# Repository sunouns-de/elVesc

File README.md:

# README

`Status: Completed (Archive State).`

This project is no longer being maintained as an active WIP. The primary reason is the availability of official VESC peripherals (such as the [VESC Dash 35B](https://www.vesclabs.com/product/vesc-dash-35b/) or the [VESC Rmcore](https://www.vesclabs.com/product/vesc-rmcore/)), which cover many of the original goals (CAN connectivity, LispBM scripting) natively and, in some aspects, more effectively.

**Important notes on the current state:**
1. **PCB Design:** The latest PCB design in this repository still contains errors. The board layout needs to be cross-checked against the schematics and revised before it can be considered fully functional.
2. **12V High-Side Switching:** Unlike many other solutions, including official ones like the RmCore, this design explicitly supports 12V high-side switching for vehicle lighting.
3. **Hardware Fixes:** The horn circuitry has already been corrected in the schematic but has not yet been implemented in the physical PCB layout.

## Overview

You find the code, flashable on an ESP32 DevKitC with PlatformIO in the submodule.

Everything needed for the PCB inside pcb-schematics.

Link to Onshape Design of Headunit Mount in directory 3d design.
Other project designs will also be added here.

## Core concept

Replacement for original board electronics and an open platform to have a tachometer for any [VESC](https://vesc-project.com/) powered E-Bike.

### Headunit (Display)

#### Implemented and working
Currently working on Tachometer:
- Speed
- Trip Kilometer (resets every power cycle)
- Time since Startup
- Average Speed
- Battery Voltage (mapped to left bar)
- Motor Current (mapped to right bar)
- Motor Power in kW (below right bar)
- Brake Lights
 - triggered when pulling any brake lever
 - also triggered when using regenerative braking above a configurable motor current

Currently all values (wheel diameter, battery voltage, max current, etc.) are hard coded.

Proper way for multiple bikes will be to utilize config files.

#### Implemented but not working
- Average Wh per km consumption
- Horn (probably hardware issue due to bad soldering)

#### Planned
- Odometer (saving distance to ESP32 flash)
- Don't try to calculate values like average speed or  but just get them from VESC

##### Ideas
- Smaller headunit but with more features: Utilizing also an ESP 32 C6 with Zigbee
 - Home Assistant integration
- OTA Updates
- Blinkers but requires more Pins on ESP32 or multiplexing
  - Also requires more than current 8 wires by using a normal RJ45-connector and Ethernet-cable to bottom or serial communication and therefore another microcontroller on the SPDB.

### Switching and Power Distribution Board (SPDB)

Converts high battery voltage to 12V for the headlights and other components. (DC
/DC converter is not cheap, but great quality and has pleanty of headroom)

Also provides 5V for the Headunit: ESP32, Hall-Effect-Brake-Levers and Display. (ESP32 runs on 3V but the dev kit converts the incoming 5V to the usable 3V)

Connects the VESC to the rest of the system.

Turns on Brakelights and also provides power for the 12V lights.

#### Planned
- components with bigger footprints for easier soldering
 - MOSFETs
 - capacitors
 - resistors

#### Ideas

- USB-C in port and DC/DC converter for charging big E-Bike battery (not _really_ practical but I really want this hehe)
- USB-C out port for charging other devices or at least another 12V out to use existing products for this
- Eventually blinkers (my L1E-class-bike came without them from the manufacturer so they are not mandatory)

In combination with Headunit: Serial connection / CAN-BUS based system.

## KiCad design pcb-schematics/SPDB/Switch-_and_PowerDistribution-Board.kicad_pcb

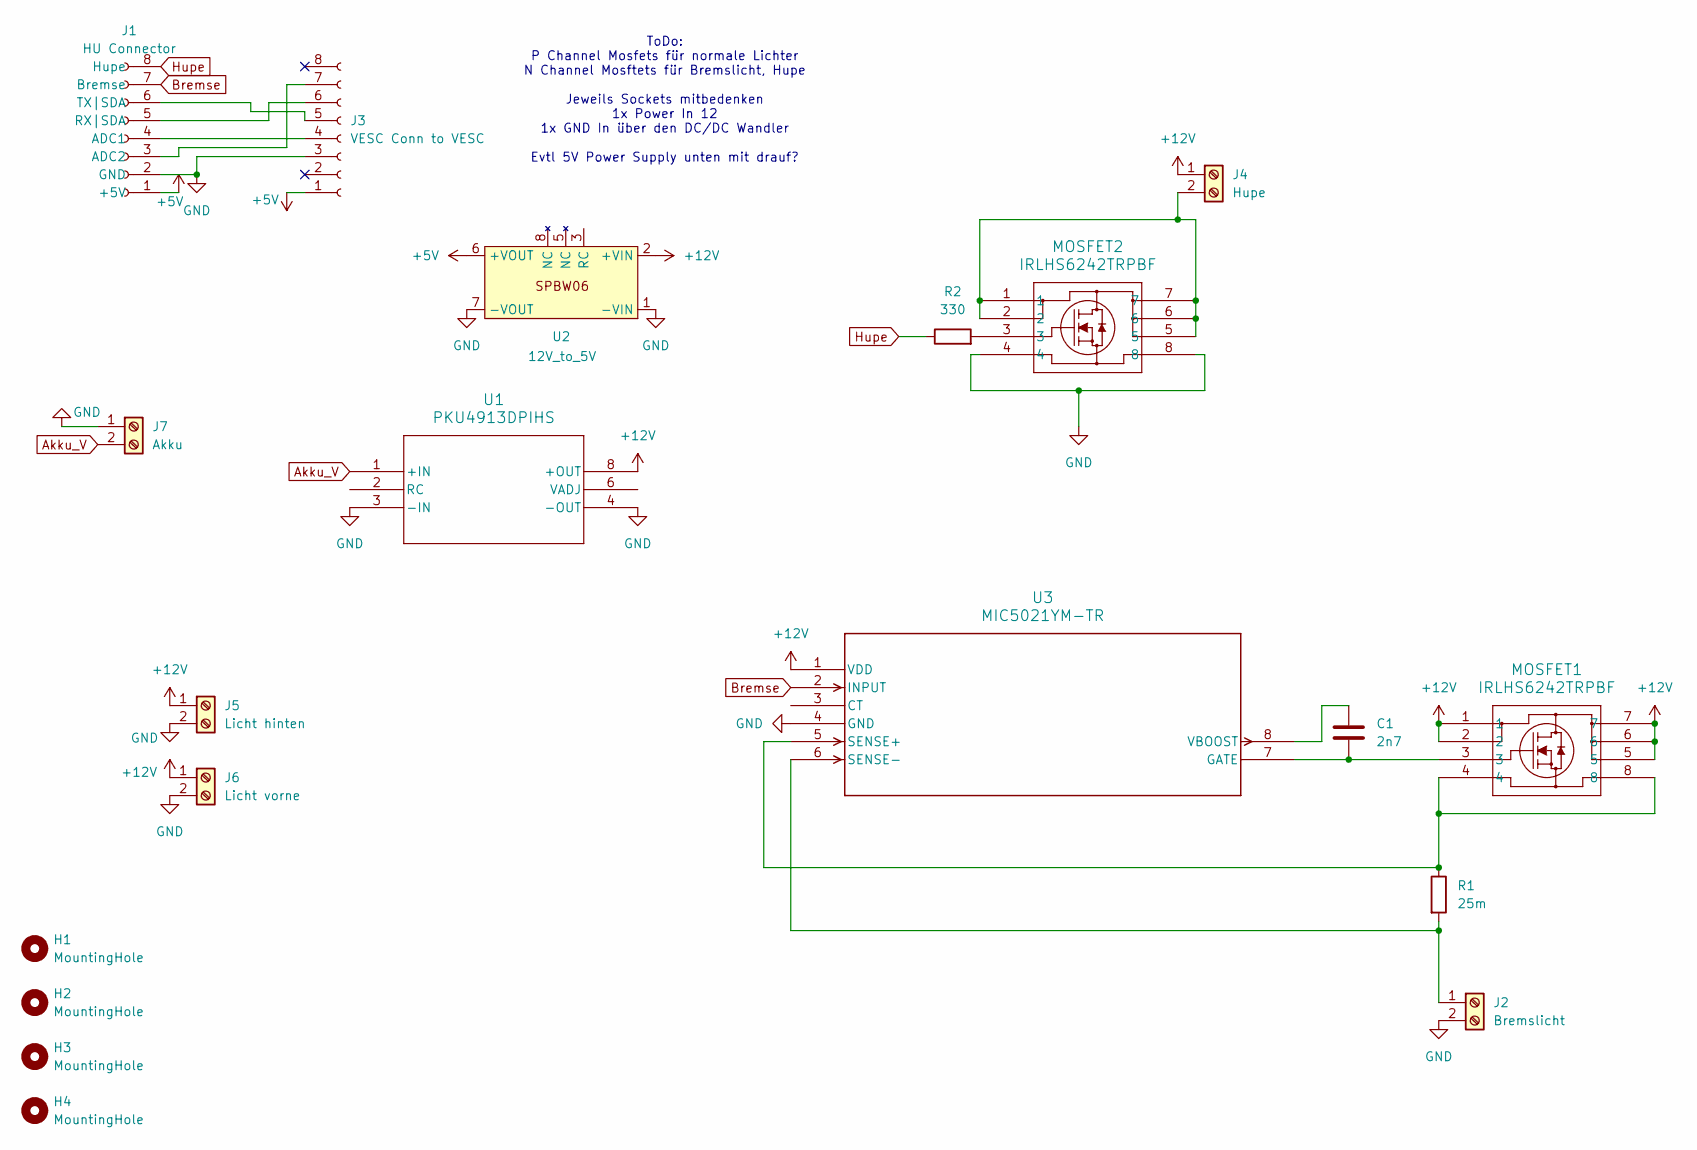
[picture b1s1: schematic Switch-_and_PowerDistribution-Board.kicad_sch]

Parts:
C1: 2n7; C_0805_2012Metric_Pad1.18x1.45mm_HandSolder
H1, H2, H3, H4: MountingHole; MountingHole_3.2mm_M3
J1: HU Connector; RJ45_Amphenol_54602-x08_Horizontal
J2: Bremslicht; TerminalBlock_bornier-2_P5.08mm
J3: VESC Conn to VESC; PinHeader_1x08_P2.54mm_Vertical
J4: Hupe; TerminalBlock_bornier-2_P5.08mm
J5: Licht hinten; TerminalBlock_bornier-2_P5.08mm
J6: Licht vorne; TerminalBlock_bornier-2_P5.08mm
J7: Akku; AMASS_XT60-F_1x02_P7.20mm_Vertical
MOSFET1, MOSFET2: IRLHS6242TRPBF; PQFN6_2X2_INF
R1: 25m; R_Axial_DIN0204_L3.6mm_D1.6mm_P5.08mm_Horizontal
R2: 330; R_Axial_DIN0204_L3.6mm_D1.6mm_P5.08mm_Horizontal
U1: PKU4913DPIHS; PKU4913DPIHS_FPM
U2: 12V_to_5V; DPBW06_MWU
U3: MIC5021YM-TR; SOIC-8_M_MCH

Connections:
+5V: J1.1 (+5V), J3.1, U2.6 (+VOUT)
+12V: J4.1, J5.1, J6.1, MOSFET1.1, MOSFET1.2, MOSFET1.5, MOSFET1.6, MOSFET1.7, U1.8 (+OUT), U2.2 (+VIN), U3.1 (VDD)
Akku_V: J7.2, U1.1 (+IN)
Bremse: J1.7 (Bremse), U3.2 (INPUT)
GND: J1.2 (GND), J2.2, J3.3, J5.2, J6.2, J7.1, MOSFET2.4, MOSFET2.8, U1.3 (-IN), U1.4 (-OUT), U2.1 (-VIN), U2.7 (-VOUT), U3.4 (GND)
Hupe: J1.8 (Hupe), R2.1
unnamed: J1.4 (ADC1), J3.4
unnamed: J1.3 (ADC2), J3.7 (Pin_2)
unnamed: J1.5 (RX|SDA), J3.6 (Pin_3)
unnamed: J1.6 (TX|SDA), J3.5 (Pin_4)
unnamed: J2.1, R1.2, U3.6 (SENSE-)
unnamed: J4.2, MOSFET2.1, MOSFET2.2, MOSFET2.5, MOSFET2.6, MOSFET2.7
unnamed: MOSFET2.3, R2.2
unnamed: C1.2, MOSFET1.3, U3.7 (GATE)
unnamed: MOSFET1.4, MOSFET1.8, R1.1, U3.5 (SENSE+)
unnamed: C1.1, U3.8 (VBOOST)

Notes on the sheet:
ToDo: P Channel Mosfets für normale Lichter N Channel Mosftets für Bremslicht, Hupe Jeweils Sockets mitbedenken 1x Power In 12 1x GND In über den DC/DC Wandler Evtl 5V Power Supply unten mit drauf?

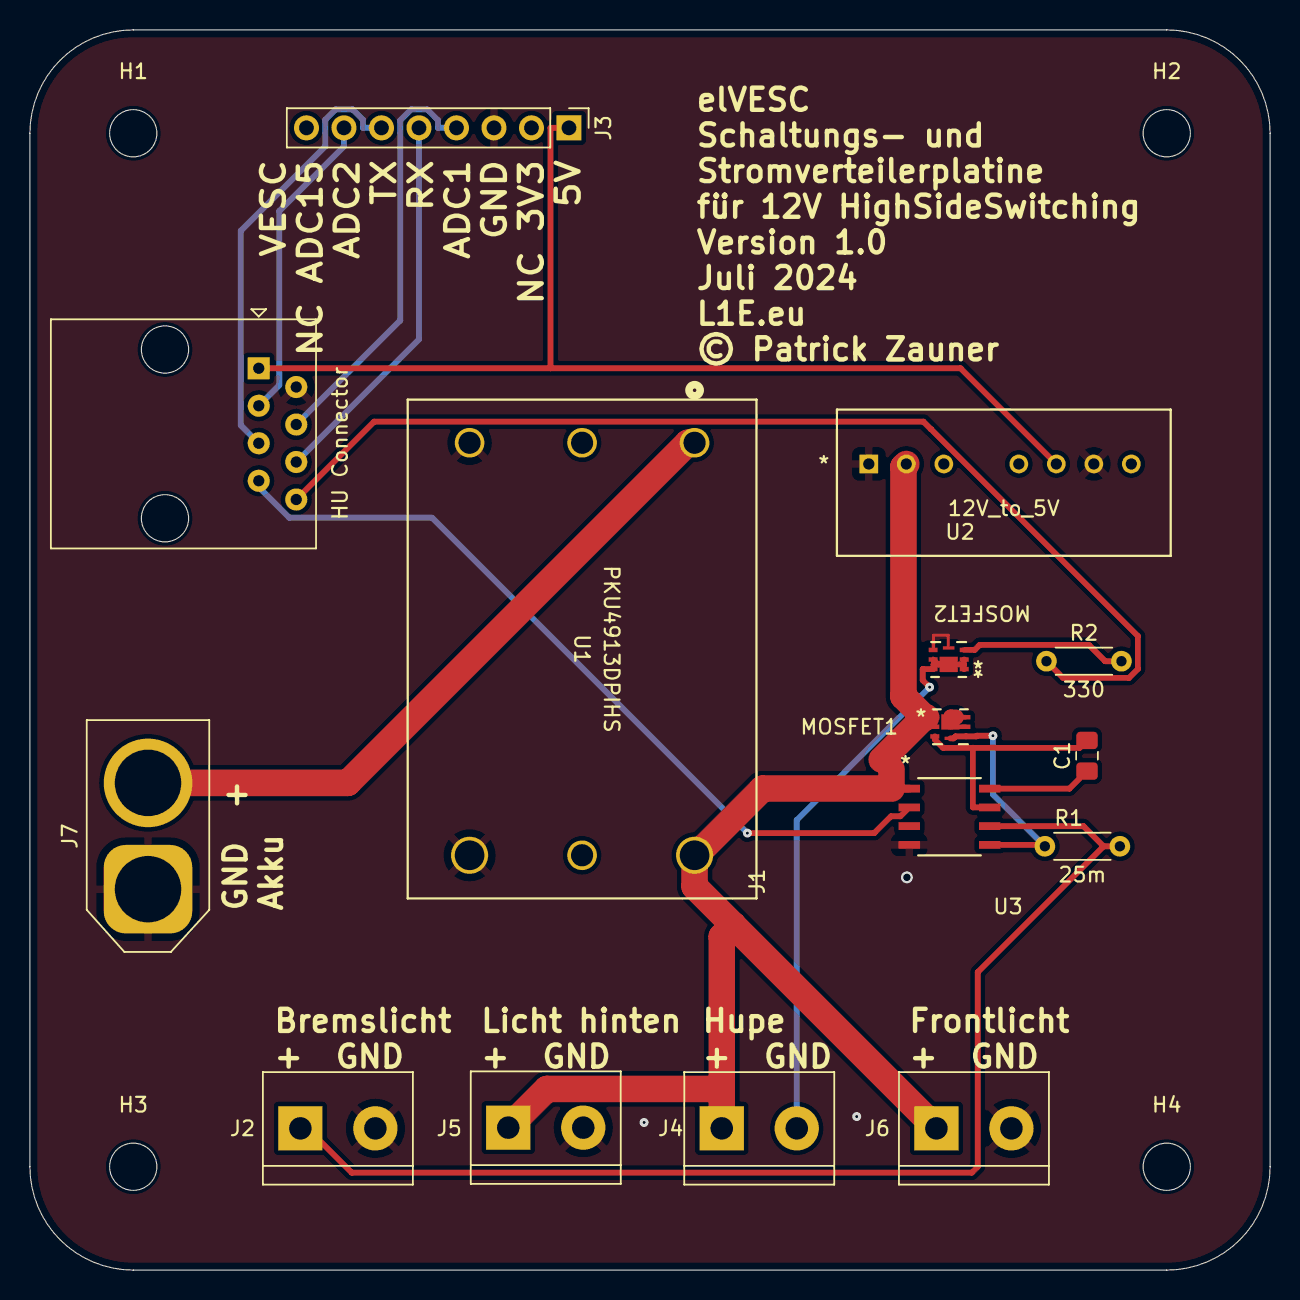
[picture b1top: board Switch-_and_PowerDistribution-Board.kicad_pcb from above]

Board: 2 copper layers, 84.0 x 84.0 mm, 19 parts (0 on the bottom side), 16 nets.

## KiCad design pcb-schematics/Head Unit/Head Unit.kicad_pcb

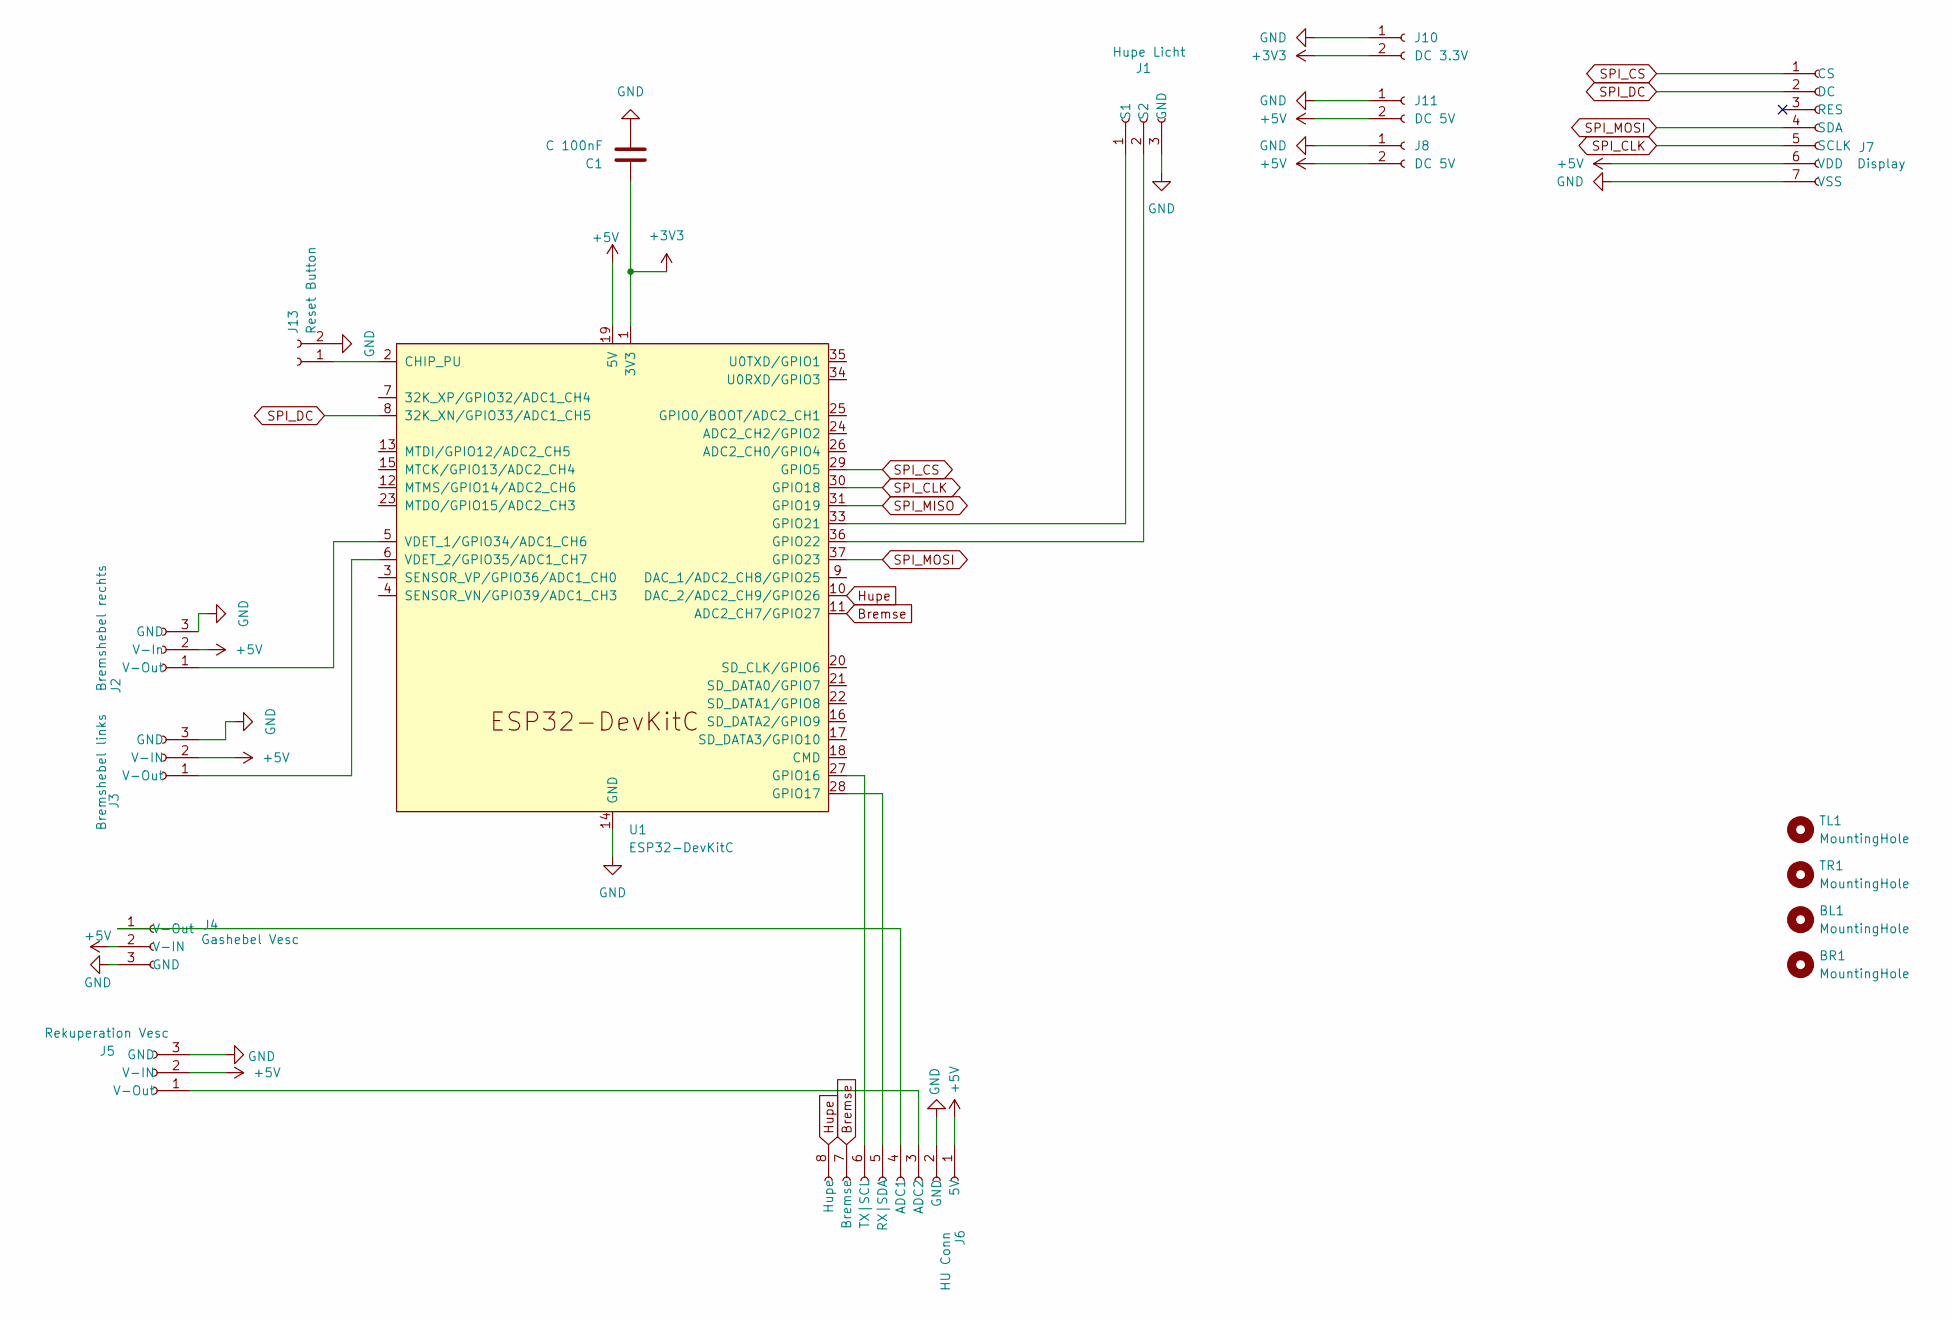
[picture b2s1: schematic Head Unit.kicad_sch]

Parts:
BL1: MountingHole; MountingHole_3.2mm_M3
BR1: MountingHole; MountingHole_3.2mm_M3
C1: C 100nF; C_Radial_D5.0mm_H5.0mm_P2.00mm
J1: Hupe Licht; PinHeader_1x03_P2.54mm_Vertical
J2: Bremshebel rechts; PinHeader_1x03_P2.54mm_Vertical
J3: Bremshebel links; PinHeader_1x03_P2.54mm_Vertical
J4: Gashebel Vesc; PinHeader_1x03_P2.54mm_Vertical
J5: Rekuperation Vesc; PinHeader_1x03_P2.54mm_Vertical
J6: HU Conn; RJ45_Amphenol_54602-x08_Horizontal
J7: Display; DIYMORE.CC
J8, J11: DC 5V; PinHeader_1x02_P2.54mm_Vertical
J10: DC 3.3V; PinHeader_1x02_P2.54mm_Vertical
J13: Reset Button; PinHeader_1x02_P2.54mm_Vertical
TL1: MountingHole; MountingHole_3.2mm_M3
TR1: MountingHole; MountingHole_3.2mm_M3
U1: ESP32-DevKitC

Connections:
+3V3: C1.1, J10.2, U1.1 (3V3)
+5V: J2.2 (V-In), J3.2 (V-IN), J4.2 (V-IN), J5.2 (V-IN), J6.1 (5V), J7.6 (VDD), J8.2, J11.2, U1.19 (5V)
Bremse: J6.7 (Bremse), U1.11 (ADC2_CH7/GPIO27)
GND: C1.2, J1.3 (GND), J2.3 (GND), J3.3 (GND), J4.3 (GND), J5.3 (GND), J6.2 (GND), J7.7 (VSS), J8.1, J10.1, J11.1, J13.2, U1.14 (GND), U1.32 (GND), U1.38 (GND)
Hupe: J6.8 (Hupe), U1.10 (DAC_2/ADC2_CH9/GPIO26)
unnamed: J1.1 (S1), U1.33 (GPIO21)
unnamed: J1.2 (S2), U1.36 (GPIO22)
unnamed: J2.1 (V-Out), U1.5 (VDET_1/GPIO34/ADC1_CH6)
unnamed: J3.1 (V-Out), U1.6 (VDET_2/GPIO35/ADC1_CH7)
unnamed: J4.1 (V-Out), J6.4 (ADC1)
unnamed: J5.1 (V-Out), J6.3 (ADC2)
unnamed: J6.5 (RX|SDA), U1.28 (GPIO17)
unnamed: J6.6 (TX|SCL), U1.27 (GPIO16)
unnamed: J13.1, U1.2 (CHIP_PU)
SPI_CLK: J7.5 (SCLK), U1.30 (GPIO18)
SPI_CS: J7.1 (CS), U1.29 (GPIO5)
SPI_DC: J7.2 (DC), U1.8 (32K_XN/GPIO33/ADC1_CH5)
SPI_MISO: U1.31 (GPIO19)
SPI_MOSI: J7.4 (SDA), U1.37 (GPIO23)

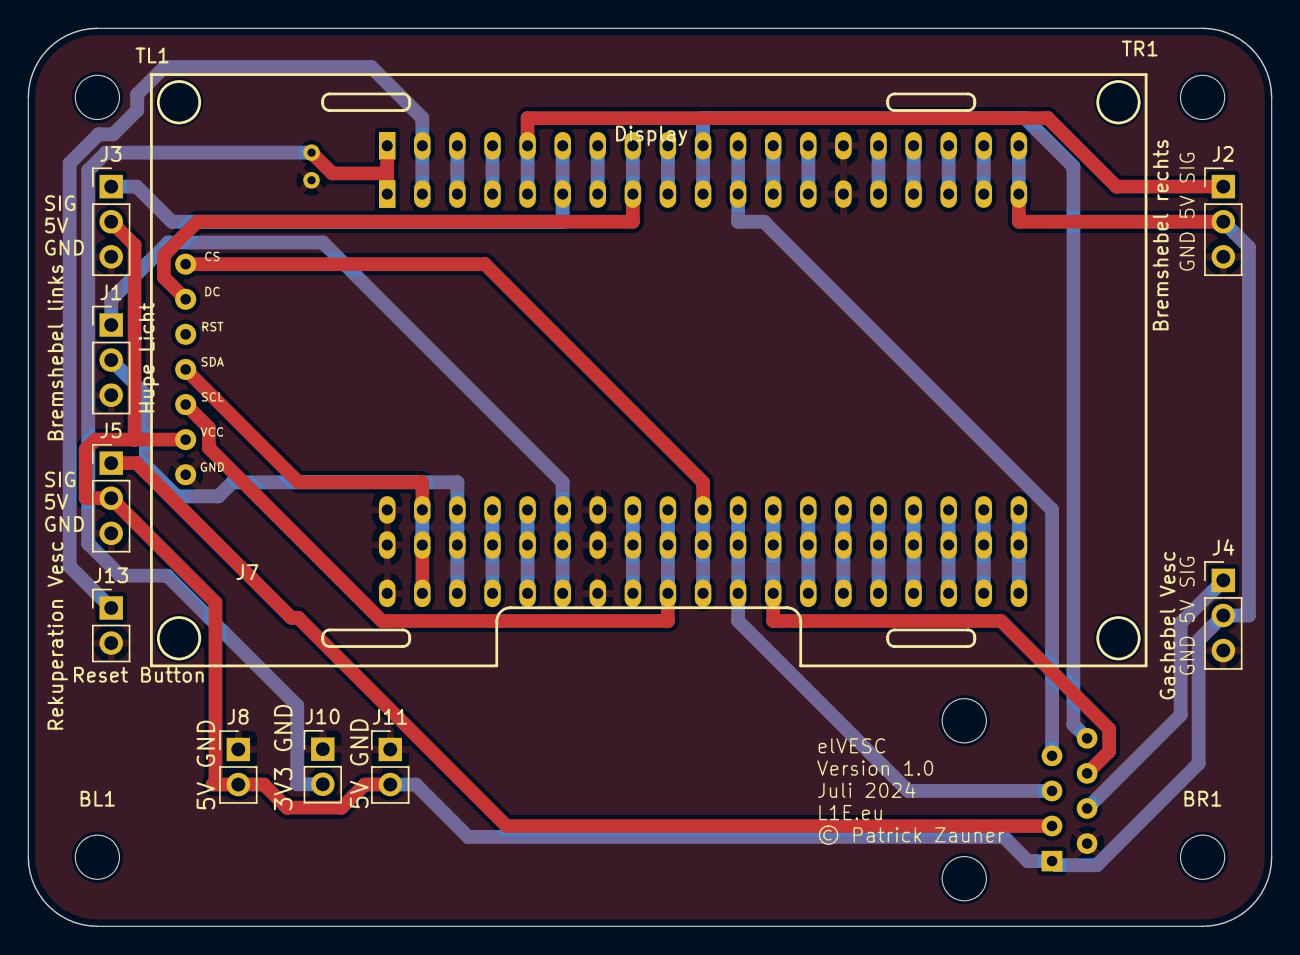
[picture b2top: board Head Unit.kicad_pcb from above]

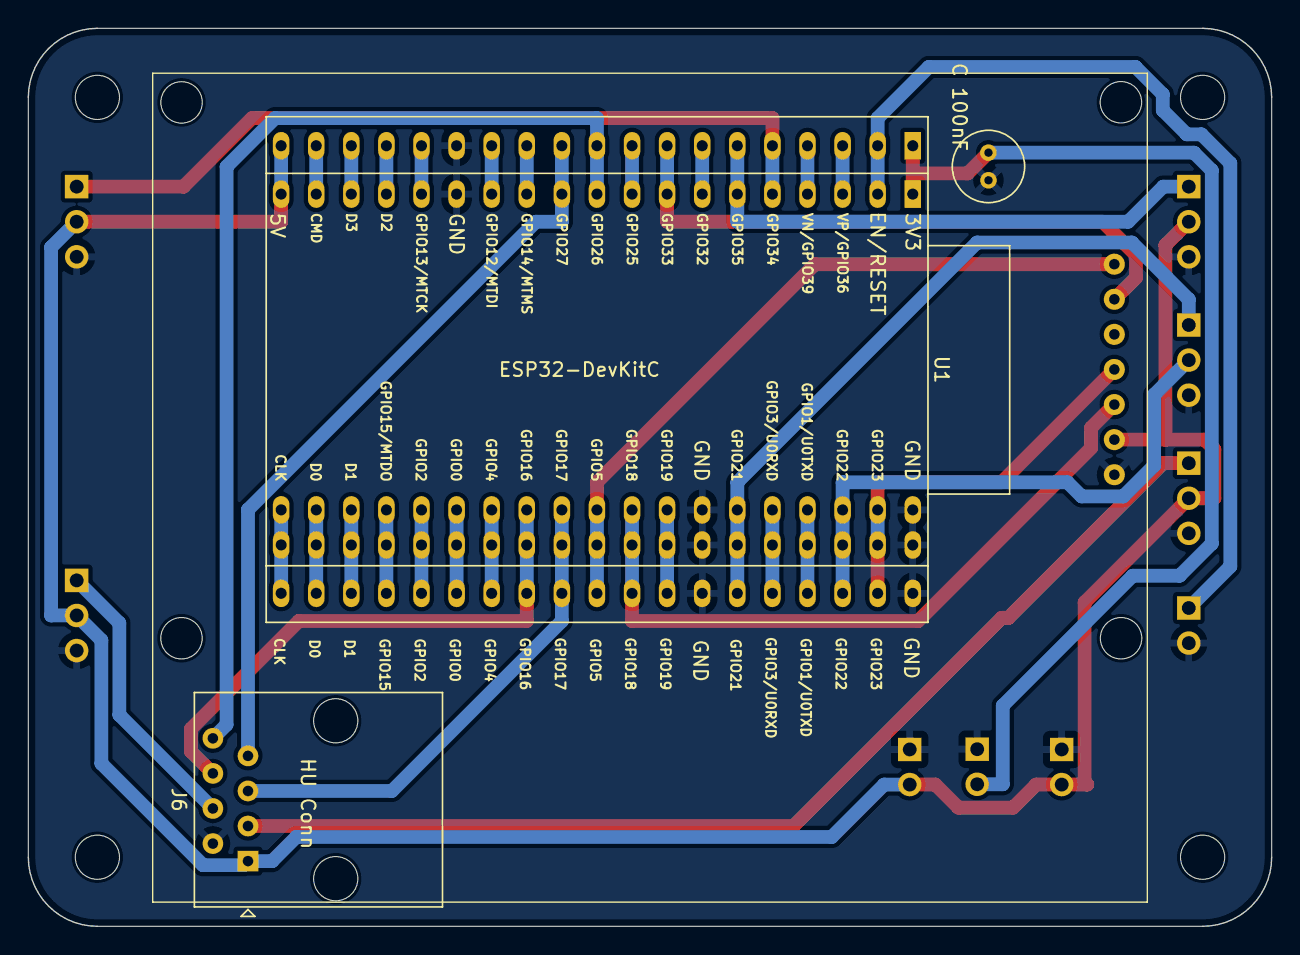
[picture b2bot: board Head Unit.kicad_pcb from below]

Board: 2 copper layers, 90.0 x 65.0 mm, 17 parts (3 on the bottom side), 18 nets.

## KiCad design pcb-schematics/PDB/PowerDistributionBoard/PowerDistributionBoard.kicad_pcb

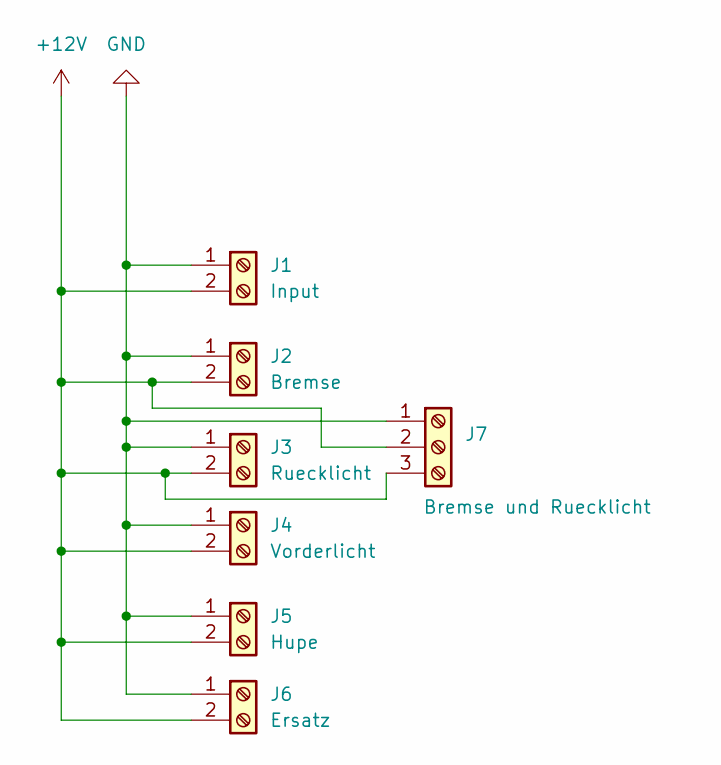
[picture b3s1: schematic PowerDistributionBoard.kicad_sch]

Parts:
J1: Input; TerminalBlock_bornier-2_P5.08mm
J2: Bremse; TerminalBlock_bornier-2_P5.08mm
J3: Ruecklicht; TerminalBlock_bornier-2_P5.08mm
J4: Vorderlicht; TerminalBlock_bornier-2_P5.08mm
J5: Hupe; TerminalBlock_bornier-2_P5.08mm
J6: Ersatz; TerminalBlock_bornier-2_P5.08mm
J7: Bremse und Ruecklicht; TerminalBlock_bornier-3_P5.08mm

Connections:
+12V: J1.2, J2.2, J3.2, J4.2, J5.2, J6.2, J7.2, J7.3
GND: J1.1, J2.1, J3.1, J4.1, J5.1, J6.1, J7.1

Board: 2 copper layers, 11 parts (0 on the bottom side), 2 nets, no tracks yet.

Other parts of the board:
BL: MountingHole_3.2mm_M3
BR: MountingHole_3.2mm_M3
TL: MountingHole_3.2mm_M3
TR: MountingHole_3.2mm_M3

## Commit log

2024-05-05 added esp32 code submodule
2024-05-05 migrate files
2024-05-16 schematics update
2024-05-16 updated schematics
2024-05-16 3.3vdc to 5vdc converter
2024-05-16 submodule version bump
2024-05-17 rücklicht wiring
2024-05-18 before 5V change
2024-05-18 all hail 5V
2024-05-30 PCB Update to 2x RJ45
2024-07-22 updated schematics, now with a design change: only 1 cable between both; resulting in always on light, updated to RJ45-Connector, so easy to plug in and standardized cables available. battery to 12v 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
    everything coming with smaller footprints. great update.
2025-05-13 updated submodule and added logo
2025-09-24 publishing
2025-09-24 added PCB overview image
2025-09-24 fixed typo in README
2025-09-24 fixed typo pt 2
2026-02-01 updated schematics, readme and added schematics as pdf files
2026-02-01 translated readme changes to english

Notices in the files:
pcb-schematics/Head Unit/Head Unit.kicad_pcb:
© Patrick Zauner
